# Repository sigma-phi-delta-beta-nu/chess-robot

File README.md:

# chess-robot
Chess robot professional project

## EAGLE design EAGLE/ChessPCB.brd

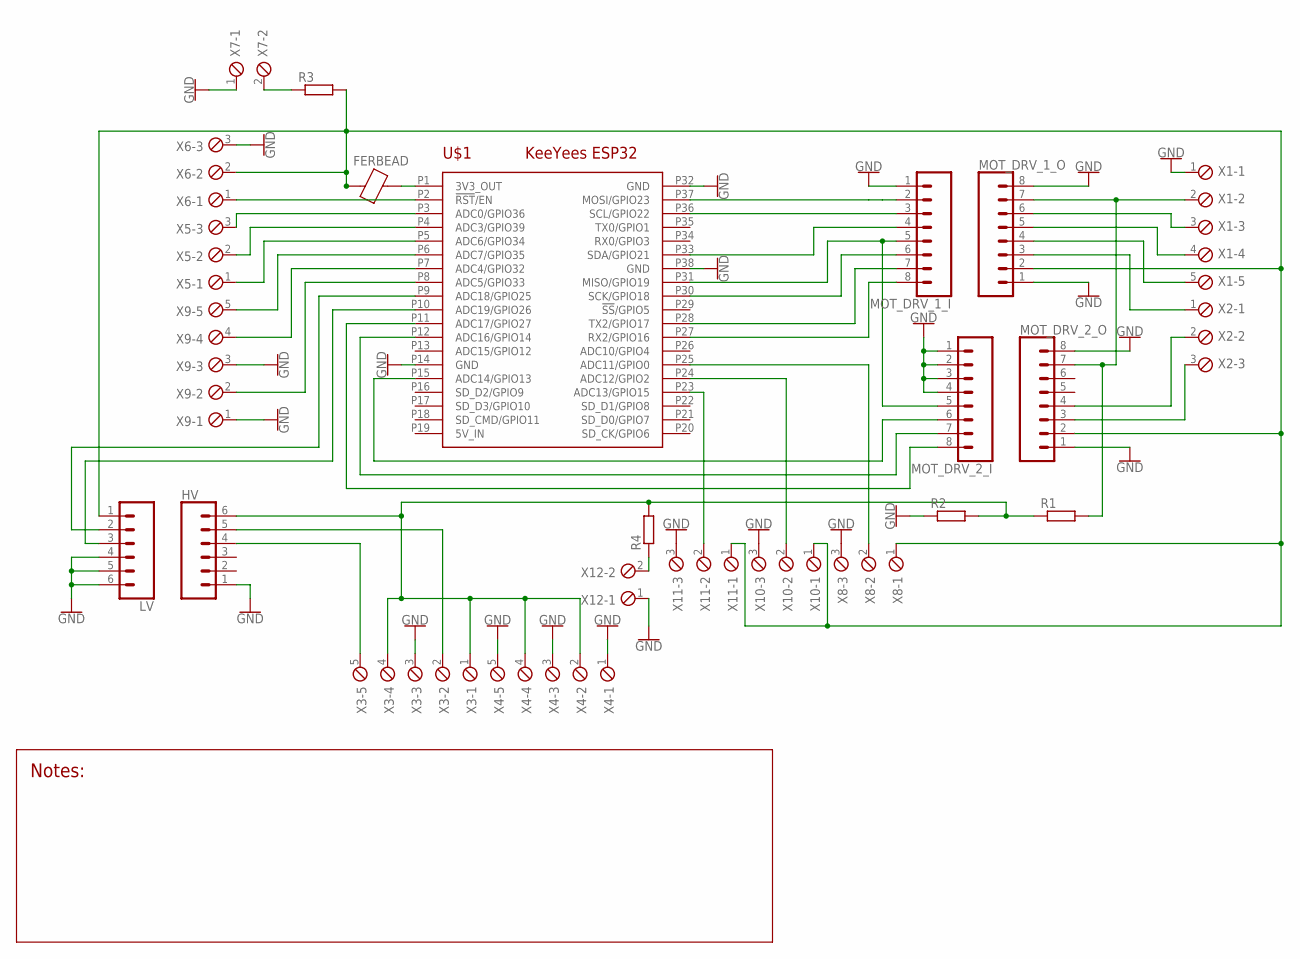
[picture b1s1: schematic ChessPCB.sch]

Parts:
FERBEAD: BEAD0402; 0402
HV: CONN_06SILK_FEMALE_PTH; 1X06
LV: CONN_06SILK_FEMALE_PTH; 1X06
MOT_DRV_1_I, MOT_DRV_1_O, MOT_DRV_2_I, MOT_DRV_2_O: CONN_08"; 1X08
R1, R2, R3, R4: R-EU_0204/7; 0204/7
U$1: KEEYEES_ESP32
X1, X3, X4, X9: SCREWTERM_5P_254; 5POL254
X2, X5, X6, X8, X10, X11: SCREWTERM_3P_254; 3POL254
X7, X12: SCREWTERM_2P_254; 2POL254

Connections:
5V_IN: U$1.P19 (5V_IN)
GND: HV.1, LV.4, LV.5, LV.6, MOT_DRV_1_I.1, MOT_DRV_1_O.1, MOT_DRV_1_O.8, MOT_DRV_2_I.1, MOT_DRV_2_I.2, MOT_DRV_2_I.3, MOT_DRV_2_I.4, MOT_DRV_2_O.1, MOT_DRV_2_O.8, R2.1, U$1.P14 (GND), U$1.P32 (GND), U$1.P38 (GND), X1.1, X3.3, X4.1, X4.3, X4.5, X6.3, X7.1, X8.3, X9.1, X9.3, X10.3, X11.3, X12.1
unnamed: MOT_DRV_1_I.2, U$1.P37 (MOSI/GPIO23)
unnamed: MOT_DRV_1_I.3, U$1.P36 (SCL/GPIO22)
unnamed: MOT_DRV_1_I.4, U$1.P33 (SDA/GPIO21)
unnamed: MOT_DRV_1_I.6, U$1.P30 (SCK/GPIO18)
unnamed: MOT_DRV_1_I.7, U$1.P28 (TX2/GPIO17)
unnamed: MOT_DRV_1_I.8, U$1.P27 (RX2/GPIO16)
unnamed: MOT_DRV_1_I.5, MOT_DRV_2_I.5, U$1.P31 (MISO/GPIO19)
unnamed: LV.3, U$1.P10 (ADC19/GPIO26)
unnamed: MOT_DRV_2_I.8, U$1.P11 (ADC17/GPIO27)
unnamed: MOT_DRV_2_I.7, U$1.P12 (ADC16/GPIO14)
unnamed: MOT_DRV_2_I.6, U$1.P15 (ADC14/GPIO13)
unnamed: U$1.P3 (ADC0/GPIO36), X5.3
unnamed: U$1.P4 (ADC3/GPIO39), X5.2
unnamed: U$1.P5 (ADC6/GPIO34), X5.1
unnamed: U$1.P6 (ADC7/GPIO35), X9.5
unnamed: U$1.P7 (ADC4/GPIO32), X9.4
unnamed: LV.2, U$1.P9 (ADC18/GPIO25)
unnamed: U$1.P8 (ADC5/GPIO33), X9.2
unnamed: MOT_DRV_2_O.3, X2.3
unnamed: FERBEAD.2, U$1.P1 (3V3_OUT)
unnamed: MOT_DRV_2_O.4, X2.2
unnamed: R3.1, X7.2
unnamed: FERBEAD.1, LV.1, MOT_DRV_1_O.2, MOT_DRV_2_O.2, R3.2, X6.2, X8.1, X10.1, X11.1
unnamed: HV.6, R1.1, R2.2, R4.2, X3.1, X3.4, X4.2, X4.4
unnamed: U$1.P25 (ADC11/GPIO0), X8.2
unnamed: U$1.P24 (ADC12/GPIO2), X10.2
unnamed: U$1.P23 (ADC13/GPIO15), X11.2
unnamed: U$1.P2 (!RST!/EN), X6.1
unnamed: HV.5, X3.2
unnamed: MOT_DRV_1_O.7, MOT_DRV_2_O.7, R1.2, X1.2
unnamed: HV.4, X3.5
unnamed: R4.1, X12.2
unnamed: MOT_DRV_1_O.6, X1.3
unnamed: MOT_DRV_1_O.5, X1.4
unnamed: MOT_DRV_1_O.4, X1.5
unnamed: MOT_DRV_1_O.3, X2.1

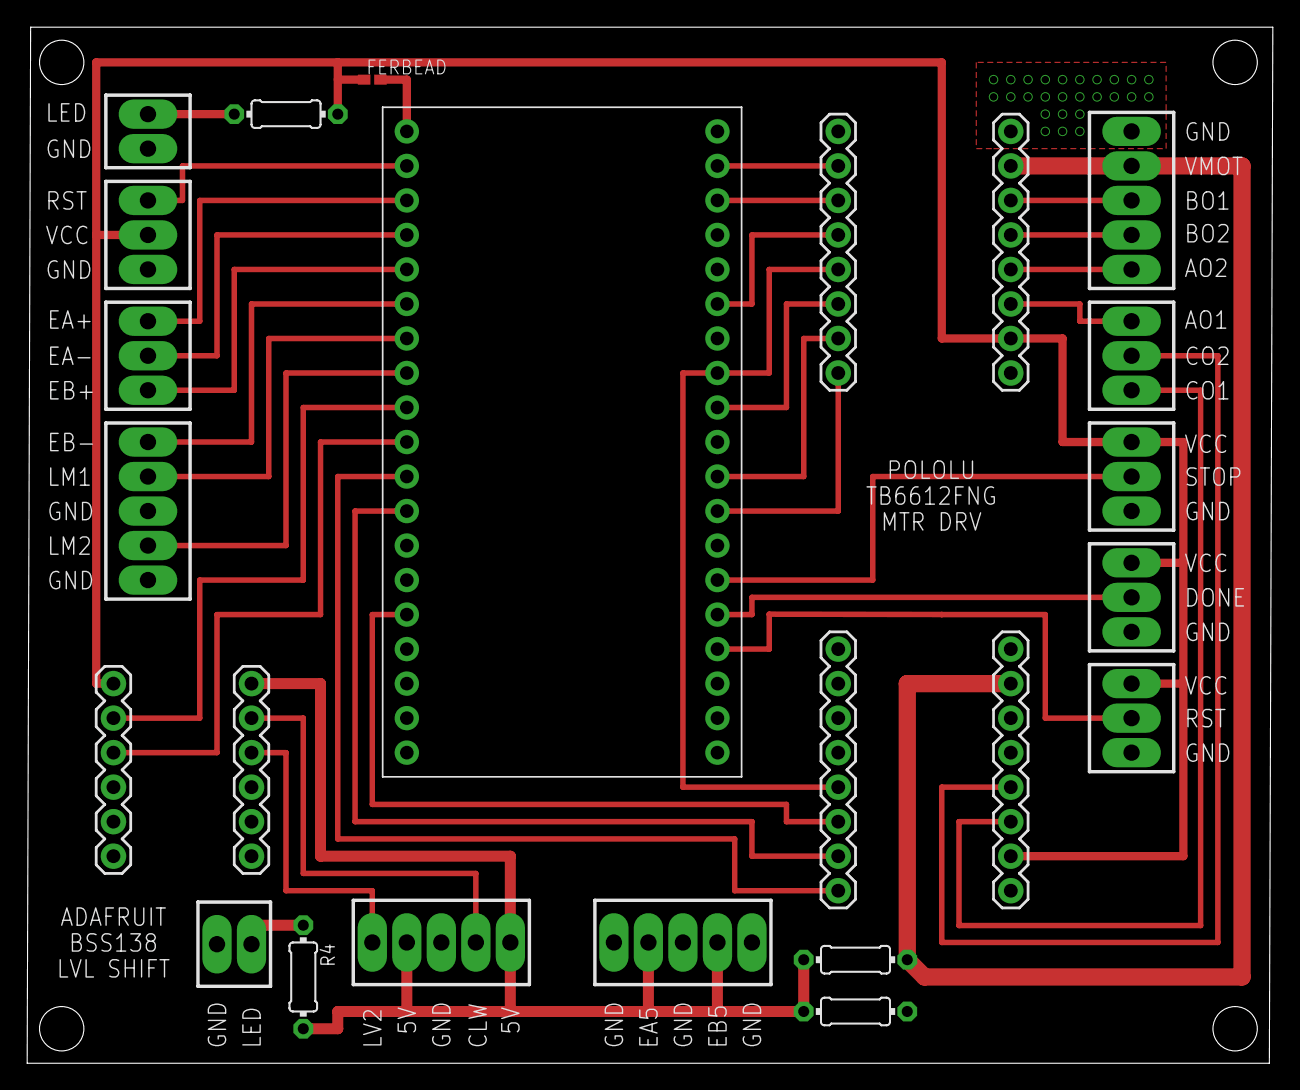
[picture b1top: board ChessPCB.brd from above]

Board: 2 copper layers, 91.7 x 76.3 mm, 24 parts (0 on the bottom side), 37 nets.

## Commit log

2023-02-03 DC Motor Control
2023-02-16 Create read_n_echo_ESP
    This is the echo code that will read values coming from the python script in the port, and send it back
2023-02-16 Create read_n_echo_Python
    The echo counterpart for the echo esp
2023-02-28 2.28 Update
2023-02-28 Update read_n_echo_Python
2023-02-28 Update 2.28 1:12pm
2023-02-28 Fixed it
2023-03-01 2.28 4:35pm
2023-03-01 python edit
2023-03-01 The read_echo is working
2023-03-01 Added Done
2023-03-01 updated a bunch of stuff
2023-03-08 task_x pin update
2023-04-20 New Tasks
2023-04-23 PCB Edits
2023-04-24 PCB Updates
2023-05-02 Python edits
2023-05-03 Create ChessGUI
2023-05-03 made into python file
2023-05-03 changed colors of board
2023-05-10 Create Call_Matlab
2023-05-10 Create chessboard
2023-05-10 Create GetCoordinate
2023-05-10 Create BoardtoFEN
2023-05-12 updated code
2023-05-12 echo works
2023-05-15 read_n_echo works again
2023-05-22 Task edits
2023-05-24 update test
2023-05-25 Limit Switch Implementation
2023-05-25 maine.py update
2023-05-25 flag update
2023-05-25 microcontroller
2023-05-26 Create Reset and Done Move Buttons
    Here is code for Reset and Done Move Buttons. There is also code for other processes that somewhat correlate to the FSM I made earlier. Lots of code for actual processes are needed in the comments
2023-05-28 homing works
2023-05-29 New update
2023-05-29 Button
2023-05-29 wait
2023-05-29 x_axis
2023-05-30 while loops
2023-05-31 base code commented
2023-06-01 Jeff is Stupid

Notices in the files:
parts and their libraries:
SparkFun-Connectors: Licensing: Creative Commons ShareAlike 4.0 International - https://creativecommons.org/licenses/by-sa/4.0
